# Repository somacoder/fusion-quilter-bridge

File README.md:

<p align="center">
  <strong>Keep your design. Change your layout.</strong><br>
  A script-first bridge from Fusion Electronics to Quilter through KiCad — and back.
</p>

<p align="center">
  <a href="#quick-start">Quick start</a> ·
  <a href="docs/workflow.md">Workflow</a> ·
  <a href="docs/validation.md">Evidence</a> ·
  <a href="#limits-not-fine-print">Limitations</a> ·
  <a href="NOTICE.md">Licensing</a>
</p>

---

## A bridge, not a replacement

Your schematic remains the source of truth. Export EAGLE 9.x from Fusion, build
a KiCad 9 project for Quilter, then translate placement and copper back into an
EAGLE script or patched board. The script is intended to update the **existing**
Fusion PCB rather than create a disconnected copy.

The conversion runs locally with **KiCad's official engine and Python's standard
library**. No CAD window automation, cloud converter, pip dependencies or telemetry
is involved. Uploading a board to Quilter is a separate, deliberate step.

| Principle | What it means |
| :--- | :--- |
| **Preserve the source** | Original schematic, embedded libraries and connectivity remain authoritative. |
| **Verify the translation** | Compare net membership, pad geometry and copper, not just whether a file opens. |
| **Make limits visible** | Known format mismatches are reported; checks are not a manufacturing sign-off. |
| **Reproduce the evidence** | An original synthetic fixture exercises the real forward and return tools. |

## Quick start

### 1 · Install the engine

**Windows is the validated platform.**

| Dependency | Purpose |
| :--- | :--- |
| [KiCad 9](https://www.kicad.org/download/windows/) | Required for forward conversion: bundled Python, `pcbnew` and `kicad-cli`. |
| KiCad 10, side by side | Independent EAGLE board import check. Required for the complete round-trip self-test. |
| Fusion Electronics | Export the original design and apply the returned script. |
| [Quilter](https://app.quilter.ai) | Actual AI placement/routing, through its web interface. |

The Windows launchers locate standard per-user and system KiCad installations.
No `pip install` is needed. Pure-Python utilities are also tested with Python 3.11.
EAGLE footprint copper polygons that contain exactly one simple SMD pad are
converted to KiCad custom-pad primitives, preserving the original copper union
and pin number. Ambiguous ownership is an error, not a guessed net assignment.
The verifier checks the copper union independently against the original EAGLE
footprint, and copper shorts now fail forward verification rather than being
waived as ordinary pre-routing errors. Unrouted connections are still expected.
Do **not** replace KiCad 9's Python with KiCad 10's `pcbnew`; the latter has caused
initialization dialogs in headless use.

### 2 · Try the public demo first

From the repository root:

```powershell
.\Fusion_to_Quilter.cmd --input examples\roundtrip-demo
.\Selftest_Roundtrip.cmd --name roundtrip-demo
```

The [demonstrator](examples/roundtrip-demo) has **12 parts, 24 pads, four nets and
an 80 × 60 mm outline**. It exercises SMD and through-hole packages, restriction
wires, smashed text, rotations, flips, copper arcs, vias and pours.

> **Synthetic test geometry, not a working circuit.** The self-test simulates
> router edits; it is not Quilter AI and intentionally need not pass electrical DRC.
> No actual Quilter job or execution inside Fusion is claimed by these tests.

### 3 · Convert your own design

1. Create an `input` folder. Export the schematic and PCB from Fusion as EAGLE
   9.x files with matching names, such as `my-board.sch` and `my-board.brd`.
2. In Fusion, finalize the board outline and pre-place parts whose positions must
   remain fixed. Quilter's treatment of in-outline parts should be confirmed in
   its preview.
3. Run:

   ```powershell
   .\Fusion_to_Quilter.cmd --name my-board
   ```

4. Review the checks. Upload the **individual** `.kicad_pcb`, `.kicad_sch` and
   `.kicad_pro` files from `to_quilter\my-board\upload` to Quilter. Do not ZIP these
   upload files. Multi-sheet schematics produce additional schematic files;
   upload all files in the generated upload folder.
5. Download the selected candidate into a `from_quilter` folder, then run:

   ```powershell
   .\Quilter_to_Fusion.cmd --name my-board
   ```

6. Back up the original Fusion design. Open the **same PCB that was exported**,
   run the printed `SCRIPT` command, then inspect the result and run RATSNEST/DRC.

See the [full workflow](docs/workflow.md) for file selection, snapshots, automation
boundaries and return-path details. GUI export/import and web uploads still require
interaction. An optional loopback receiver supports browser-agent downloads without
the Save dialog; this project does not submit jobs or bypass account restrictions.

## What is checked

| Layer of evidence | Scope |
| :--- | :--- |
| Source comparison | Net names/members, part inventory, pad connectivity, copper and package keep-outs. |
| KiCad CLI | Exported schematic netlist, schematic/PCB parity and board outline. |
| Independent importer | KiCad 10 reads the EAGLE board and compares geometry with the converted/result PCB. |
| Round-trip self-test | Identity, simulated full layout, then a routed second pass. |
| Script model | Interprets the generated EAGLE commands and compares with the patched board. |

The public demo passed all three round-trip scenarios on Windows with KiCad
9.0.8 and 10.0.7. [Recorded scope and reproduction commands →](docs/validation.md)

The GitHub workflow runs **Python-only regression checks**, not the KiCad
integration suite. A green CI badge must not be interpreted as board certification.

## Limits, not fine print

This is **research software**, not a universal lossless converter.

* Return translation covers part placement, tracks, arcs, vias and supported copper
  pours. The original outline, drawing content and libraries are retained rather
  than replaced from the router's file.
* Known unsupported cases include router-created rule areas, teardrops and holes
  within pours. Some pour semantics differ between formats. Read every warning.
* Connectivity changes are not applied to the Fusion schematic. A router result
  that differs in connectivity must be investigated, not accepted as a new design.
* Locked parts, free holes and vias below Fusion restring limits have special
  behavior; see [return limitations](docs/workflow.md#return-limitations).
* The EAGLE-script interpreter is a **test model**, not Autodesk Fusion. It cannot
  prove live editor selection behavior, 3D linkage, cloud history or every script
  interaction. Validate on a backup before adopting the result.
* Conversion checks do not certify clearance, impedance, current capacity,
  component placement, thermal performance or manufacturability.

## Contribute without leaking a design

Start with the [synthetic example](examples/roundtrip-demo), read
[CONTRIBUTING.md](CONTRIBUTING.md), and submit a minimal reproducer.
User inputs, generated output, logs and local configuration are ignored.
An [explicit release inventory](tools/check_release.py) controls package contents.
Never attach proprietary schematics, libraries or raw logs to a public issue.

## License & acknowledgement

Original code, documentation and synthetic examples: **[MIT](LICENSE)**.
Lab/Penn branding is **excluded** from that license. KiCad is installed separately
and retains its own license. This is an independent interoperability project;
no endorsement by Penn, Autodesk, KiCad or Quilter is implied.

[Provenance and release authority](NOTICE.md) ·
[Maintainer publishing checklist](docs/publishing.md) ·
[Standalone presentation](docs/index.html)

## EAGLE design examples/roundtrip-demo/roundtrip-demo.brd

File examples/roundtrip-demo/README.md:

# The round-trip demonstrator

An original **80 x 60 mm, two-layer** synthetic fixture with **12 parts, 24 pads
and four nets**. It mixes through-hole and surface-mount packages, smashed labels,
and asymmetric package restriction wires.

**Not a working circuit. Do not manufacture it.** Its routing simulator deliberately
creates geometric stress cases and may create shorts and clearance violations.
Passing conversion checks demonstrates representational agreement, not electrical
correctness or manufacturability.

All CAD here is newly generated from [generate.py](generate.py), using only Python's
standard library. No third-party package library or research design is required.

From the repository root, on Windows with KiCad 9 and 10 installed:

```powershell
.\Fusion_to_Quilter.cmd --input examples\roundtrip-demo
.\Selftest_Roundtrip.cmd --name roundtrip-demo
```

The second command tests unchanged return, simulated placement/routing, and a
second forward/return pass. It exercises rotations, flips, tracks, arcs, vias,
solid and hatched pours, removal/replacement of pours, and smashed text movement.
It is a **simulator**, not an actual Quilter job or execution in Fusion.

To regenerate the two source files:

```powershell
python examples\roundtrip-demo\generate.py
```

Generated outputs and logs remain ignored. Share only this synthetic fixture when
reporting a problem.

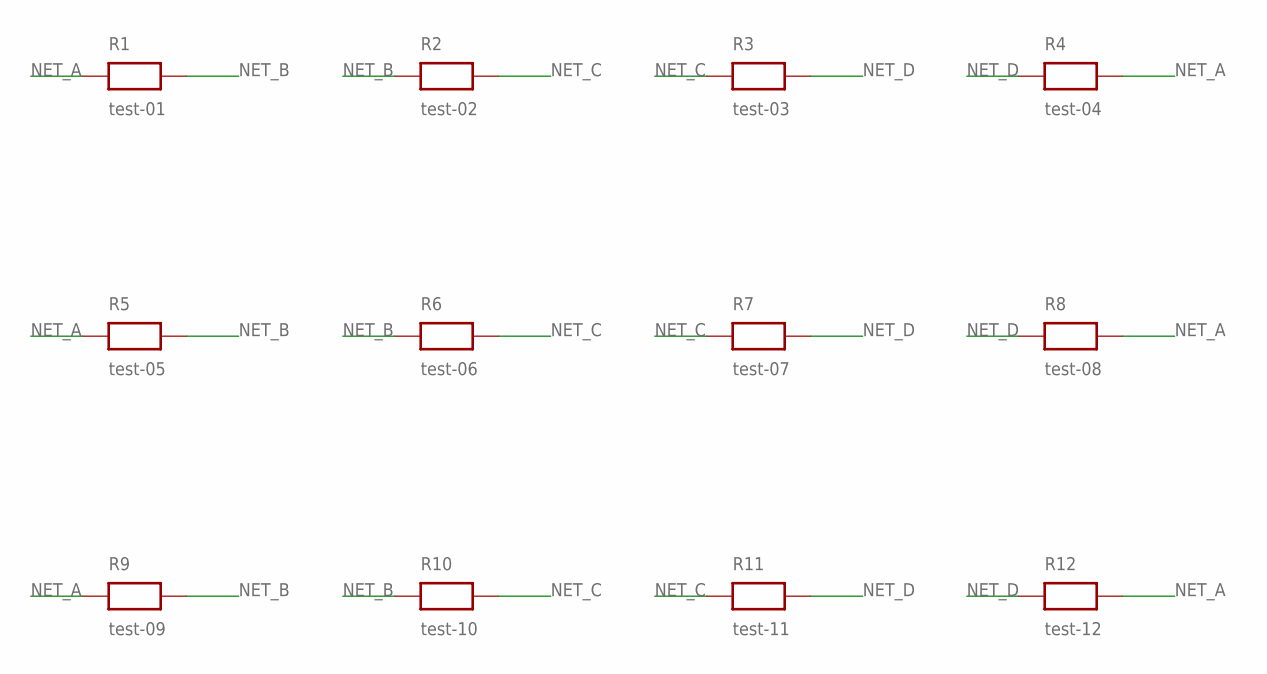
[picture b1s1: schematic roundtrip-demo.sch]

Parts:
R1: test-01; DEMO_THT
R2: test-02; DEMO_SMD
R3: test-03; DEMO_SMD
R4: test-04; DEMO_THT
R5: test-05; DEMO_SMD
R6: test-06; DEMO_SMD
R7: test-07; DEMO_THT
R8: test-08; DEMO_SMD
R9: test-09; DEMO_SMD
R10: test-10; DEMO_THT
R11: test-11; DEMO_SMD
R12: test-12; DEMO_SMD

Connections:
NET_A: R1.1 (A), R4.2 (B), R5.1 (A), R8.2 (B), R9.1 (A), R12.2 (B)
NET_B: R1.2 (B), R2.1 (A), R5.2 (B), R6.1 (A), R9.2 (B), R10.1 (A)
NET_C: R2.2 (B), R3.1 (A), R6.2 (B), R7.1 (A), R10.2 (B), R11.1 (A)
NET_D: R3.2 (B), R4.1 (A), R7.2 (B), R8.1 (A), R11.2 (B), R12.1 (A)

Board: 2 copper layers, 12 parts (0 on the bottom side), 4 nets, no tracks yet.
